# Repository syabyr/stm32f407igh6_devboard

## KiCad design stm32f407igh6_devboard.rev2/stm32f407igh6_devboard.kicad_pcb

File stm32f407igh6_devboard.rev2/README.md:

# stm32f407igh6_devboard

## 最小焊接要求
* BYPASS_REG下拉到地,使能内部LDO
* VDDA必须接到+3V3上

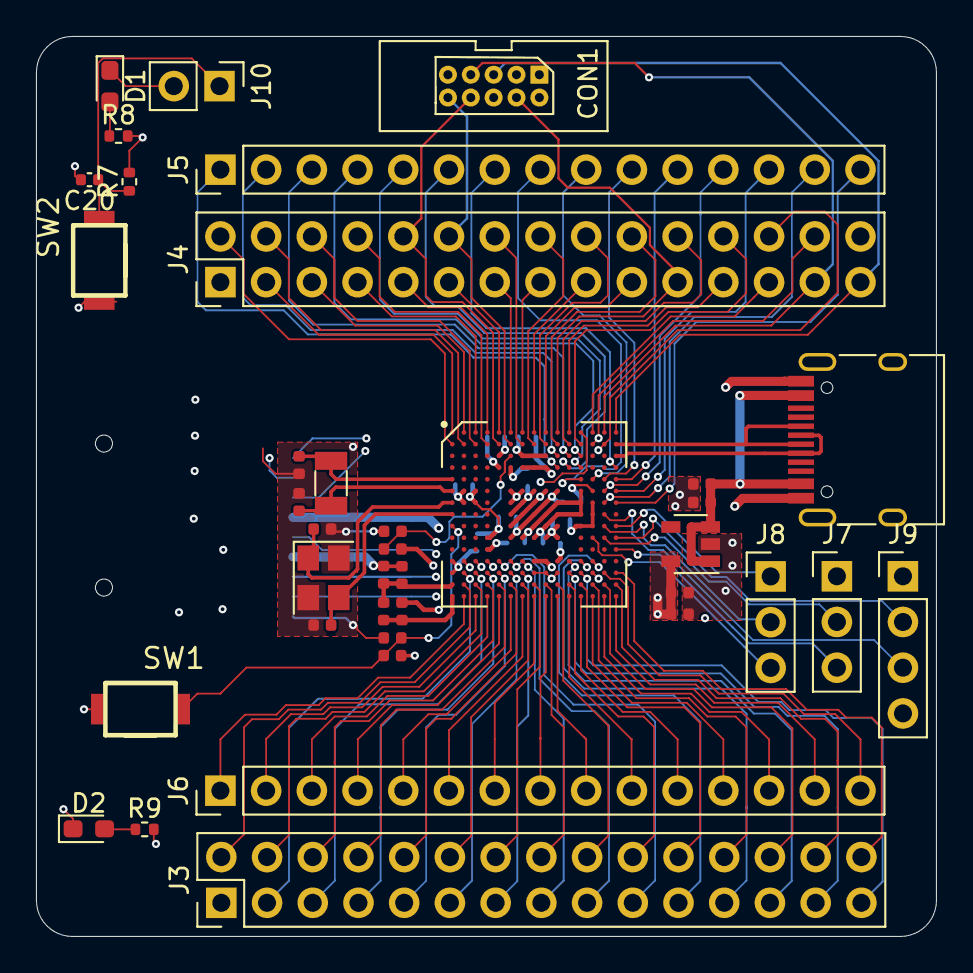
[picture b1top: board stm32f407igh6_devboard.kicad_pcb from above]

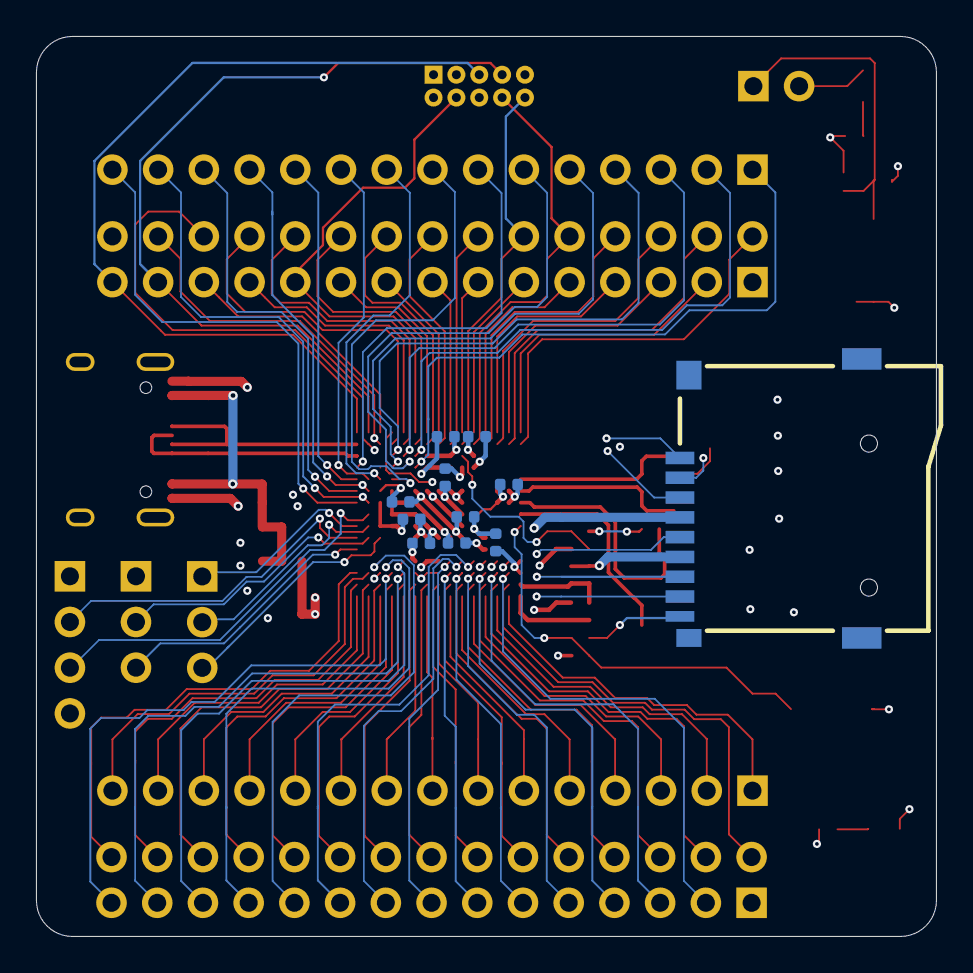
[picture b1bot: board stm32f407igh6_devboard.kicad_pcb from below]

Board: 4 copper layers, 50.0 x 50.0 mm, 49 parts (11 on the bottom side), 116 nets.

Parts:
C1, C9, C11, C13, C14, C16, C18, C20: 1uF; C_0402_1005Metric
C2, C3: 2.2uF; C_0402_1005Metric
C4, C10, C12, C15, C17, C19: 100n; C_0402_1005Metric
C5, C6, C7, C8: 20P; C_0402_1005Metric
CON1: CORTEX-DEBUGGER; debugger_2x05_P1.27mm_Vertical
D1, D2: LED; LED_0603_1608Metric_Pad1.05x0.95mm_HandSolder
J1: USB_C
J2: Micro_SD_Card; TFCARD
J3, J4: Conn_02x15_Odd_Even; PinHeader_2x15_P2.54mm_Vertical
J5, J6: Conn_01x15; PinHeader_1x15_P2.54mm_Vertical
J7, J8: Conn_01x03; PinHeader_1x03_P2.54mm_Vertical
J9: Conn_01x04; PinHeader_1x04_P2.54mm_Vertical
J10: Conn_01x02; PinHeader_1x02_P2.54mm_Vertical
L1: L; L_0402_1005Metric
R1, R8, R9: 47; R_0402_1005Metric
R2, R3, R4, R5, R6, R7: 10k; R_0402_1005Metric
SW1, SW2: SW_Push; turtlekey
U1: STM32F407IGHx; BGA-225_15x15_10.0x10.0mm
U2: LD3985M33R_SOT23; SOT-23-5
Y1: Crystal_GND24_Small; Crystal_SMD_3225-4Pin_3.2x2.5mm
Y2: Crystal; Crystal_SMD_3215-2Pin_3.2x1.5mm

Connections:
+3V3: C11.1, C12.2, C14.1, C15.2, C16.1, C17.2, C18.1, C19.2, CON1.3, J2.4, J3.1, J4.1, J4.30, L1.1, R3.2, R6.2, R7.2, R8.2, R9.2, U1.C5, U1.C7, U1.C8, U1.C9, U1.F3, U1.G3, U1.G13, U1.H13, U1.J12, U1.J13, U1.K4, U1.N8, U1.N9, U1.N10, U2.5
/stm32f407igh6/OSC8IN: C5.1, U1.G1, Y1.1
/stm32f407igh6/OSC8OUT: C6.1, U1.H1, Y1.3
/stm32f407igh6/OSC32IN: C8.1, U1.E1, Y2.2
/stm32f407igh6/OSC32OUT: C7.1, U1.F1, Y2.1
GND: C1.2, C2.2, C3.1, C4.1, C5.2, C6.2, C7.2, C8.2, C9.2, C10.1, C11.2, C12.1, C13.2, C14.2, C15.1, C16.2, C17.1, C18.2, C19.1, C20.2, CON1.6, CON1.9, D2.1, J1.A1, J1.A12, J1.B1, J1.B12, J1.S1, J2.6, J2.9, J7.1, J9.1, J9.4, R2.2, R4.1, R5.2, SW1.1, SW2.1, U1.D5, U1.D7, U1.D8, U1.D9, U1.F2, U1.F6, U1.F7, U1.F8, U1.F9, U1.F10, U1.F12, U1.G2, U1.G6, U1.G7, U1.G8, U1.G9, U1.G10, U1.G12, U1.H6, U1.H7, U1.H8, U1.H9, U1.H10, U1.H12, U1.J6, U1.J7, U1.J8, U1.J9, U1.J10, U1.K6, U1.K7, U1.K8, U1.K9, U1.K10, U1.M1, U1.M8, U1.M9, U1.N1, U2.2, Y1.2, Y1.4
NRST: C13.1, CON1.2, R6.1, SW1.2, U1.J1
unnamed: C1.1, C4.2, R1.2, U1.P1
unnamed: C2.1, U1.M10
unnamed: C3.2, U1.F13
unnamed: C20.1, J10.1, R7.1, SW2.2
unnamed: D1.1, J10.2
unnamed: D1.2, R8.1
unnamed: D2.2, R9.1
unnamed: R2.1, U1.L4
unnamed: R3.1, R4.2, U1.C6
unnamed: R5.1, U1.D6
PA0: J3.5, U1.N3
PA1: J3.3, U1.N2
PA2: J3.2, U1.P2
PA3: J6.1, U1.R2
PA4: J3.7, U1.N4
PA5: J3.6, U1.P4
PA6: J3.4, U1.P3
PA7: J6.2, U1.R3
PA8: J5.13, U1.F15
PA9: J5.11, U1.E15
PA10: J5.7, U1.D15
PA11: J1.A7, J1.B7, U1.C15
PA12: J1.A6, J1.B6, U1.B15
PA13: CON1.5, J4.29, U1.A15
PA14: CON1.7, J4.27, U1.A14
PA15: J4.25, U1.A13
PB0: J6.4, U1.R5
PB1: J6.3, U1.R4
PB2: J3.17, U1.M6
PB3: CON1.4, J4.21, U1.A10
PB4: J4.19, U1.A9
PB5: J4.13, U1.A6
PB6: CON1.10, J4.12, U1.B6
PB7: CON1.8, J4.10, U1.B5
PB8: J4.11, U1.A5
PB9: J4.8, U1.B4
PB10: J6.11, U1.R12
PB11: J6.12, U1.R13
PB12: J3.22, U1.P12
PB13: J3.24, U1.P13
PB14: J6.13, U1.R14
PB15: J6.14, U1.R15
PC3: J3.19, U1.M5
PC4: J3.9, U1.N5
PC5: J3.8, U1.P5
PC7: J5.15, U1.G15
PC8: J2.7, J5.14, U1.G14
PC9: J2.8, J5.12, U1.F14
PC10: J2.1, J4.26, U1.B14
PC11: J2.2, J4.28, U1.B13
PC12: J2.5, U1.A12
PD0: J4.24, U1.B12
PD1: J5.4, U1.C12
PD2: J2.3, J5.5, U1.D12
PD3: J5.6, U1.D11
PD4: J5.1, U1.D10
PD5: J5.3, U1.C11
PD6: J4.22, U1.B11
PD7: J4.23, U1.A11
PD8: J3.28, U1.P15
PD9: J3.26, U1.P14
PD10: J3.30, U1.N15
PD11: J6.15, U1.N14
PE0: J4.9, U1.A4
PE1: J4.7, U1.A3
PE2: J4.5, U1.A2
PE3: J4.3, U1.A1
PE4: J4.2, U1.B1
PE5: J4.4, U1.B2
PE6: J4.6, U1.B3
PE7: J6.7, U1.R8
PE8: J3.14, U1.P8
PE9: J3.16, U1.P9
PE10: J6.8, U1.R9
PE11: J3.18, U1.P10
PE12: J6.9, U1.R10
PE13: J3.27, U1.N11
PE14: J3.20, U1.P11
PE15: J6.10, U1.R11
PF11: J6.5, U1.R6
PF12: J3.10, U1.P6
PF13: J3.11, U1.N6
PF14: J6.6, U1.R7
PF15: J3.12, U1.P7
PG0: J3.13, U1.N7
PG1: J3.15, U1.M7
PG2: J7.3, U1.L15
PG3: J9.2, U1.K15
PG4: J7.2, U1.K14
PG5: J8.3, U1.K13
PG6: J8.1, U1.J15
PG7: J8.2, U1.J14
PG8: J9.3, U1.H14
PG9: J5.2, U1.C10
PG10: J4.20, U1.B10
PG11: J4.18, U1.B9
PG12: J4.16, U1.B8
PG13: J4.17, U1.A8
PG14: J4.15, U1.A7
PG15: J4.14, U1.B7
PH6: J3.25, U1.M11
PH7: J3.29, U1.N12
PH8: J3.23, U1.M12
PH9: J3.21, U1.M13
PH13: J5.8, U1.E12
PH14: J5.9, U1.E13
PI0: J5.10, U1.E14
VBUS: C9.1, C10.2, J1.A4, J1.A9, J1.B4, J1.B9, U2.1, U2.3
VDDA: L1.2, R1.1, U1.R1

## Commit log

2021-02-04 devboard
2021-02-05 readme
2021-08-12 rev2
2021-08-14 test
2021-08-14 ds_store
